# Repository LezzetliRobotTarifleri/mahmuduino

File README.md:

# mahmuduino

Bu projede Eagle mekaniklerini öğrenmek için çok ama çok basit bir kart yapacağız. Aklımdaki fikir tam olarak şu: Lezzetli Robot Tarifleri’nin ilk zamanlarındaki Arduino Tarifleri serisini hatırlarsanız. Çok basit donanımlar ile basit Arduino programlama serisiydi. Bu yayında o seri boyunca anlatılan komutları çalıştırıp test etmek için basit bir kart yapalım. Üzerinde dijital ve analog birimler olsun. Amaç kullanışlı havalı bir kart yapmak değil. Amacımı Eagle öğrenmeye çalışmak. İlerleyen bölümlerde daha havalı kartlar yapıyor ve yeteneklerimiz geliştiriyor olacağız. Önce kafamızda belirsizleri bir ortadan kaldıralım.

[Eagle Ne ile Başlayıp, Sıfırdan Kart Çizip, Üretime Göndereceğiz!](https://lezzetlirobottarifleri.com/eagle-ne-ile-baslayip-sifirdan-kart-cizip-uretime-gonderecegiz/)

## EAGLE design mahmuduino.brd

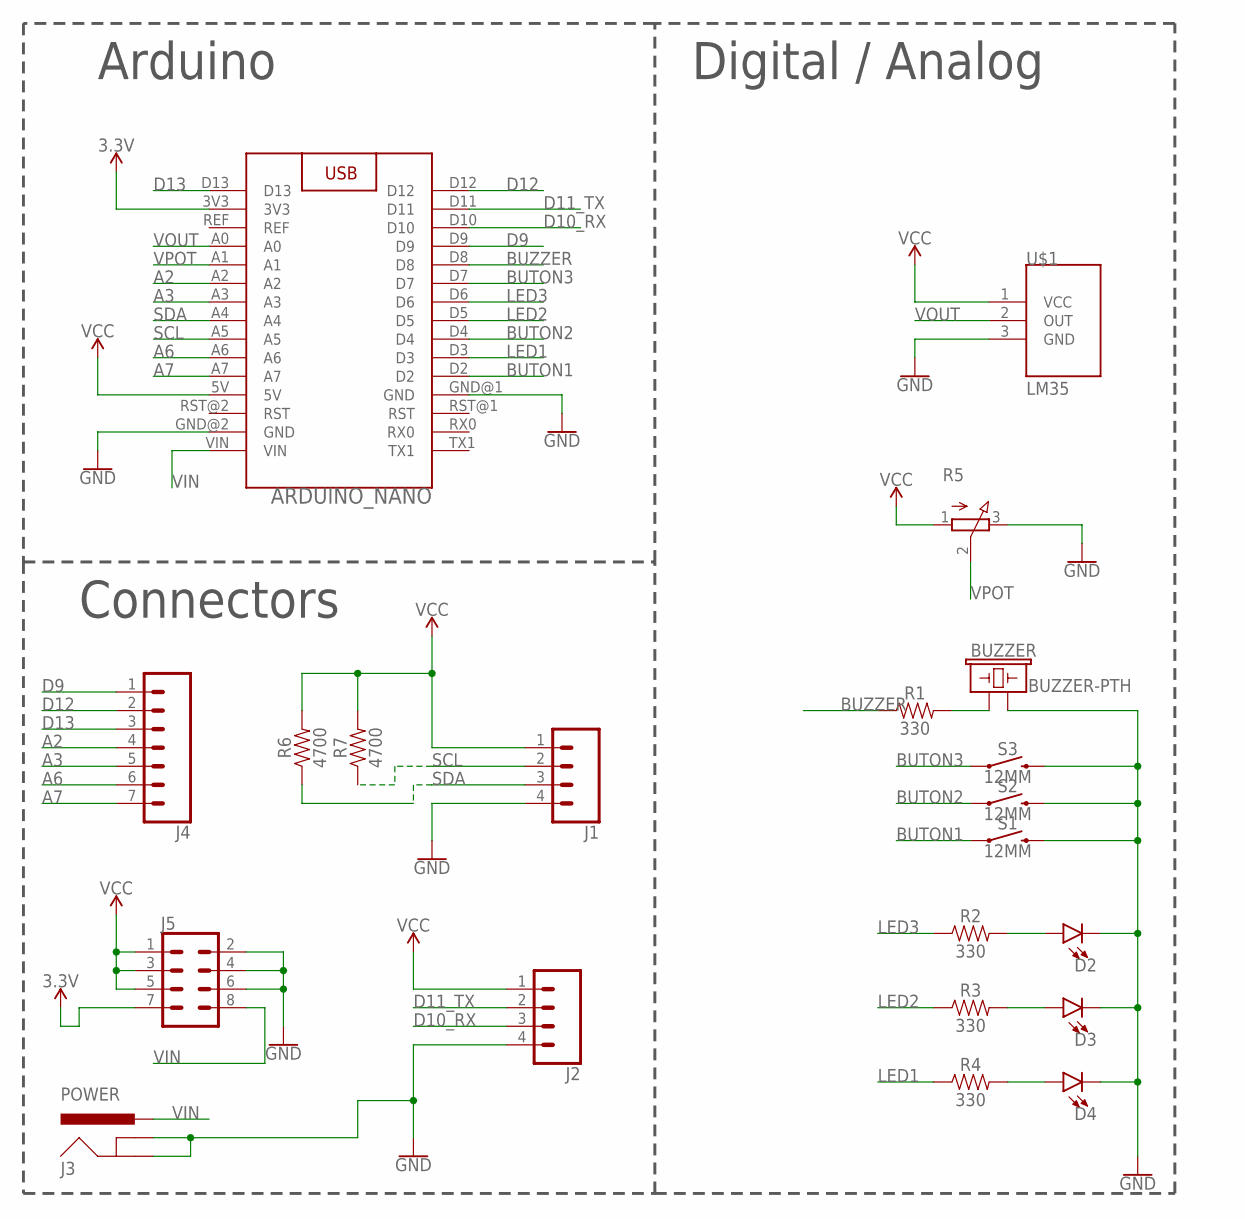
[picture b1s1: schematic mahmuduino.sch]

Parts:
ARDUINO_NANO: ARDUINO_NANO
BUZZER: BUZZER-PTH; BUZZER-12MM
D2, D3, D4: LED-3MM-NO_SILK; LED_3MM-NS
J1, J2: CONN_04; 1X04
J3: POWER; POWER_JACK_PTH
J4: CONN_07; 1X07
J5: CONN_04X2; 2X4
R1, R2, R3, R4: 330; AXIAL-0.3
R5: 3RP/1610N
R6, R7: 4700; AXIAL-0.3
S1, S2, S3: 12MM; TACTILE_SWITCH_PTH_12MM
U$1: LM35; TO-92

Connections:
3.3V: ARDUINO_NANO.3V3, J5.7
A2: ARDUINO_NANO.A2, J4.4
A3: ARDUINO_NANO.A3, J4.5
A6: ARDUINO_NANO.A6, J4.6
A7: ARDUINO_NANO.A7, J4.7
BUTON1: ARDUINO_NANO.D2, S1.1
BUTON2: ARDUINO_NANO.D4, S2.1
BUTON3: ARDUINO_NANO.D7, S3.1
BUZZER: ARDUINO_NANO.D8, R1.P$1 (1)
D9: ARDUINO_NANO.D9, J4.1
D10_RX: ARDUINO_NANO.D10, J2.3
D11_TX: ARDUINO_NANO.D11, J2.2
D12: ARDUINO_NANO.D12, J4.2
D13: ARDUINO_NANO.D13, J4.3
GND: ARDUINO_NANO.GND@1 (GND), ARDUINO_NANO.GND@2 (GND), BUZZER.- (2), D2.K (C), D3.K (C), D4.K (C), J1.4, J2.4, J3.GND, J3.GNDBREAK, J5.2, J5.4, J5.6, R5.3 (E), S1.3 (2), S2.3 (2), S3.3 (2), U$1.3 (GND)
LED1: ARDUINO_NANO.D3, R4.P$1 (1)
LED2: ARDUINO_NANO.D5, R3.P$1 (1)
LED3: ARDUINO_NANO.D6, R2.P$1 (1)
unnamed: BUZZER.+ (1), R1.P$2 (2)
unnamed: D2.A, R2.P$2 (2)
unnamed: D3.A, R3.P$2 (2)
unnamed: D4.A, R4.P$2 (2)
SCL: ARDUINO_NANO.A5, J1.2, R7.P$1 (1)
SDA: ARDUINO_NANO.A4, J1.3, R6.P$1 (1)
VCC: ARDUINO_NANO.5V, J1.1, J2.1, J5.1, J5.3, J5.5, R5.1 (A), R6.P$2 (2), R7.P$2 (2), U$1.1 (VCC)
VIN: ARDUINO_NANO.VIN, J3.PWR, J5.8
VOUT: ARDUINO_NANO.A0, U$1.2 (OUT)
VPOT: ARDUINO_NANO.A1, R5.2 (S)

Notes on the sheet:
Arduino
Connectors
Digital / Analog

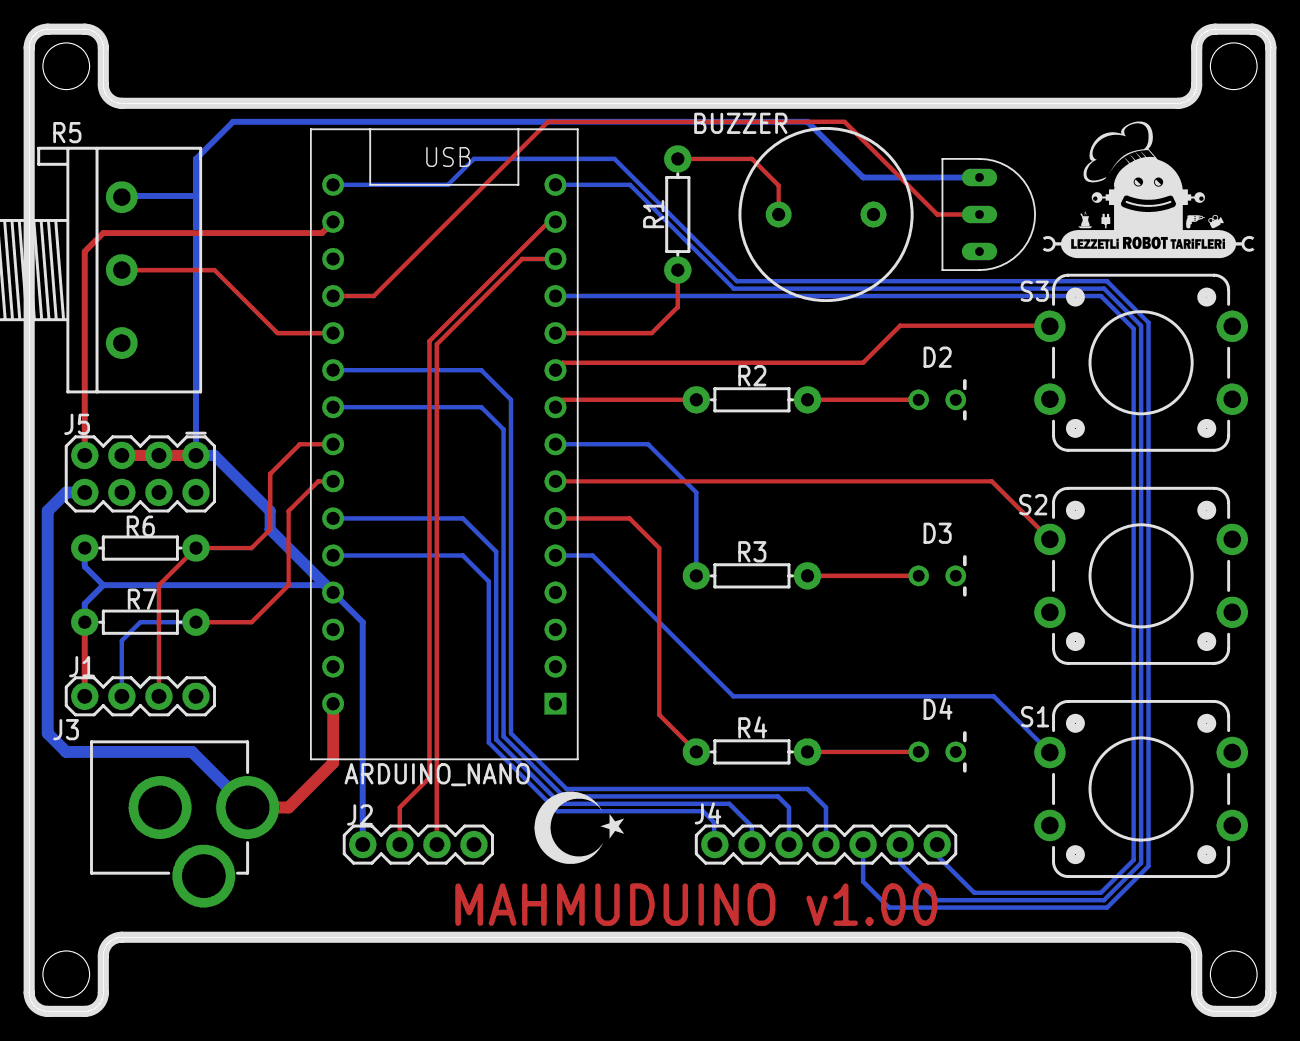
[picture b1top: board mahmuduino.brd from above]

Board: 2 copper layers, 85.1 x 67.3 mm, 24 parts (1 on the bottom side), 28 nets.

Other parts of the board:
U$2, U$3: LRT-LOGO-0,0125-B
U$9: TR_MINI

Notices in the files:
parts and their libraries:
SparkFun-LED: Licensing: Creative Commons ShareAlike 4.0 International - https://creativecommons.org/licenses/by-sa/4.0
